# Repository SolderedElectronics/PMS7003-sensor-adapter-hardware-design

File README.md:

# PMS7003 sensor adapter Hardware Design

## About the Product

|  |
| :----------------------------------------------------------: |
| [Buy PMS7003 sensor adapter](https://www.solde.red/333058) |

To connect to our PMS7003 air quality sensor easily, we designed this adapter. It allows you to connect the PMS7003 sensor to breadboard or to connect with cables.

---

## Repository Contents

This repository contains all design files for PMS7003 sensor adapter, organized as follows:

- **`CAD` folder**: Contains KiCAD design files, including:
  - Schematics
  - PCB layout
  - Panel PCB layout
  - Source 3D files in Fusion360, if any
  - All files are sorted by version with a detailed change log.
- **`OUTPUTS` folder**: Includes all production-ready files, such as:
  - Bill of Materials (BOM) and interactive BOM (iBOM)
  - PDF versions of schematics
  - 3D `.step` file of the board
  - 3D-printable models
  - Gerber files for PCB manufacturing
  - Image of the pinout of the board
  - Product image
  - Compliance, legal and generic sales documents

Refer to the `Change Log` in the CAD folder for details about updates between versions.

---

## Learn More About the Product

Beyond the repository, explore the following resources:

### Soldered Verify

The **Soldered Verify** system ensures every board you purchase from Soldered is fully functional. It also provides access to exclusive test data for your product. To get started, find the unique Soldered Verify ID on your product's packaging and enter the ID on the [Soldered Verify page](https://soldered.com/verify/) to access test results and additional product details.

### Soldered Community

Soldered Community is your go-to place for technical support. Our engineers track and answer all questions posted there, and it’s a great space for the maker community. Get answers to your questions and solutions for your challenges at [Soldered Community](https://soldered.com/community).

### solde.red

solde.red is an ultimate URL shortener and information hub. Access it by typing solde.red/ followed by your product SKU, e.g., [solde.red/333000](https://solde.red/333000), to find getting-started guides, datasheets, open-source hardware and software files, certifications, images, pinouts, and more. Read more about the shortener [here](https://solde.red/info/).

---

## Contributing

Contributions are welcome! Here’s how you can get involved:

- Submit pull requests to enhance the design or fix issues.
- Report bugs or problems by opening an issue.

We encourage community collaboration to make this product even better.

---

## About Soldered

[Soldered for Makers](https://soldered.com) specializes in designing and manufacturing electronic products tailored for enthusiasts, ranging from hobbyists to professionals. Our portfolio includes electronic boards, sensors, and actuators that are widely utilized in fields such as microelectronics, mechatronics, robotics, programming, and IoT. Every product we offer is designed in-house and built upon open-source hardware and software platforms. Proudly certified and manufactured within the European Union, our catalog likely includes the product you need for your project.

We complement these products with comprehensive tutorials and manuals, product descriptions, schematics, programming codes, and project examples. Our round-the-clock [customer and technical support](https://soldered.com/community) is available for all our products, irrespective of the sales channel. Soldered’s success and services reflect our maker community’s unwavering [trust](https://www.trustpilot.com/review/soldered.com), for which we are deeply grateful. Join our community and create using Soldered products.

---

## License

All Soldered open-source hardware (OSH) is under The TAPR Open Hardware License. Read more in the LICENSE file located in this repository.

**Disclaimer:**

No warranty - all designs in this repository are distributed in the hope that they will be useful, but without any warranty. They are provided "AS IS", therefore without warranty of any kind, either expressed or implied. The entire quality and performance of what you do with the contents of this repository are your responsibility. In no event Soldered Electronics will be liable for your damages, or losses, including any general, special, incidental, or consequential damage arising out of the use or inability to use the contents of this repository. 

---

## Have fun!

Thank you for your support from your fellow makers at Soldered Electronics.

Happy Making!

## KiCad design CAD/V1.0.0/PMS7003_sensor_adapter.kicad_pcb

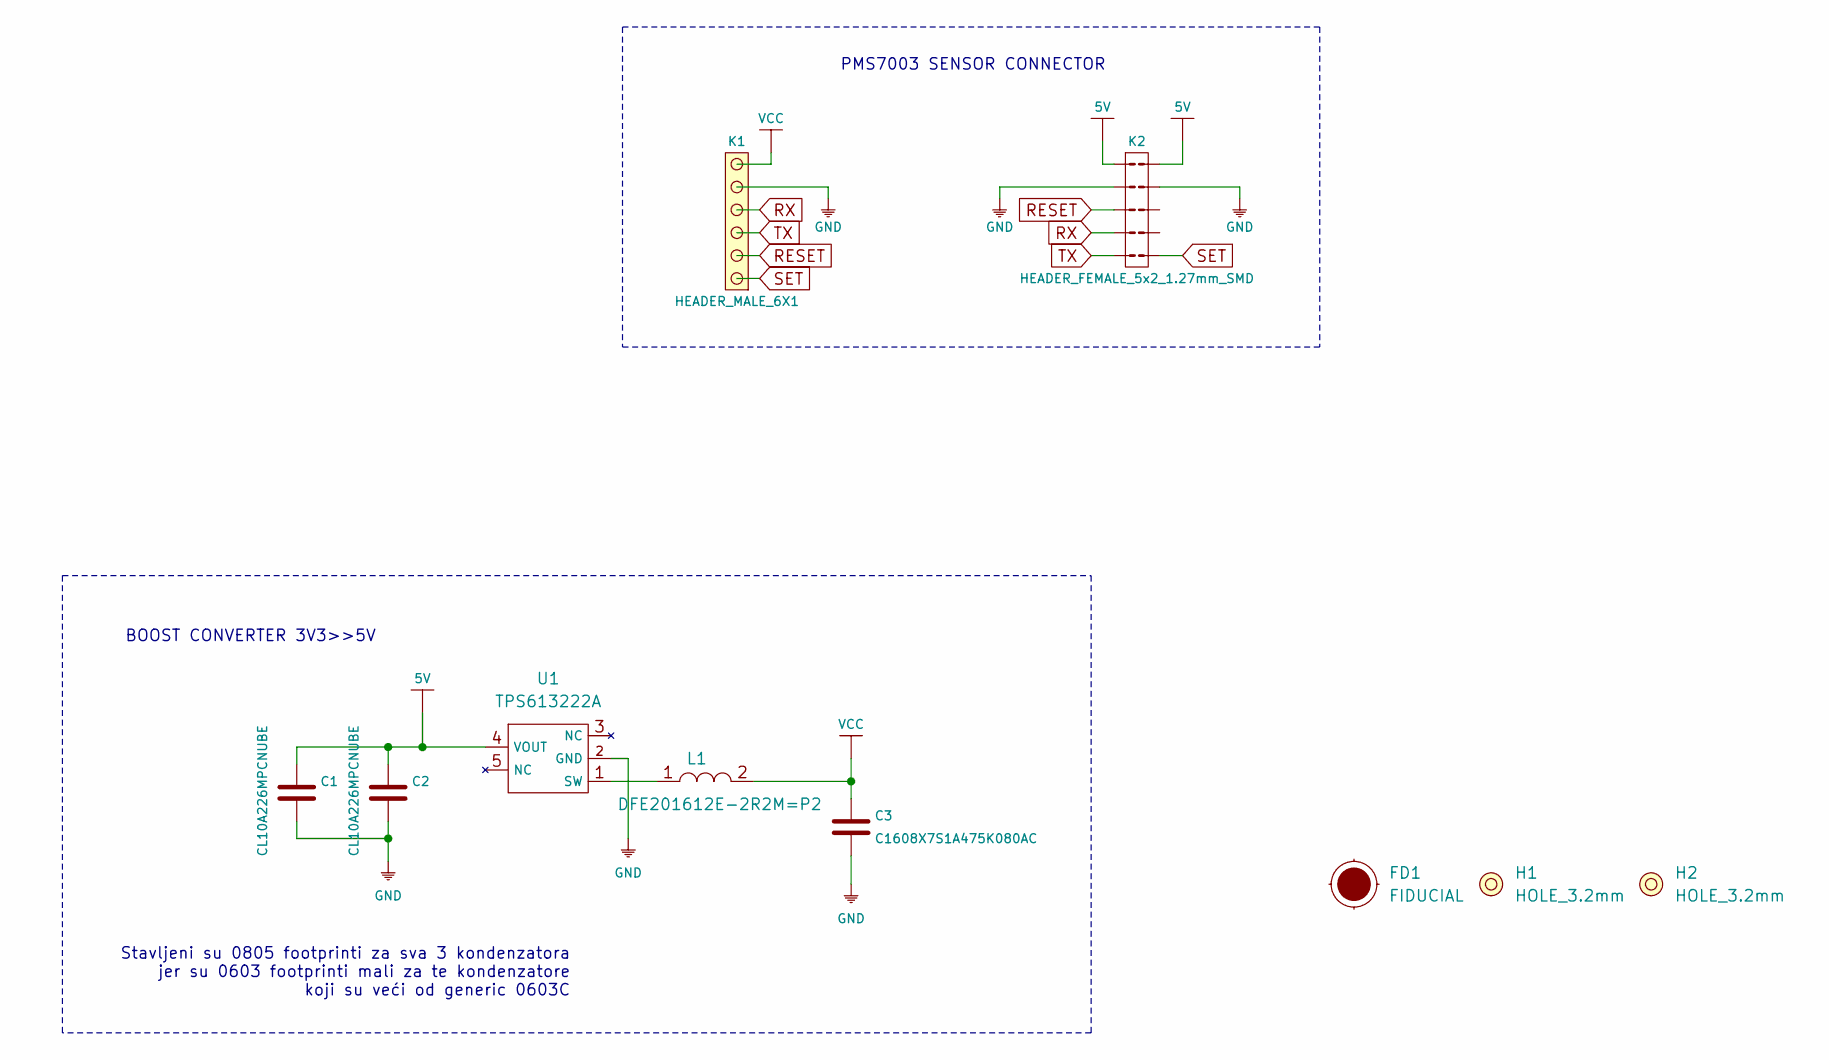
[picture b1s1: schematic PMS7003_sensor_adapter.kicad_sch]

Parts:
C1, C2: CL10A226MPCNUBE; 0805C
C3: C1608X7S1A475K080AC; 0805C
FD1: FIDUCIAL; FIDUCIAL_23
H1, H2: HOLE_3.2mm
K1: HEADER_MALE_6X1
K2: HEADER_FEMALE_5x2_1.27mm_SMD
L1: DFE201612E-2R2M=P2; 0806L
U1: TPS613222A; tps613222a

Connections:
5V: C1.2, C2.2, K2.1, K2.10, U1.4 (VOUT)
GND: C1.1, C2.1, C3.1, K1.5, K2.2, K2.9, U1.2 (GND)
unnamed: L1.1, U1.1 (SW)
RESET: K1.2, K2.3
RX: K1.4, K2.4
SET: K1.1, K2.6
TX: K1.3, K2.5
VCC: C3.2, K1.6, L1.2

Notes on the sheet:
BOOST CONVERTER 3V3>>5V
Stavljeni su 0805 footprinti za sva 3 kondenzatora jer su 0603 footprinti mali za te kondenzatore koji su veći od generic 0603C
PMS7003 SENSOR CONNECTOR

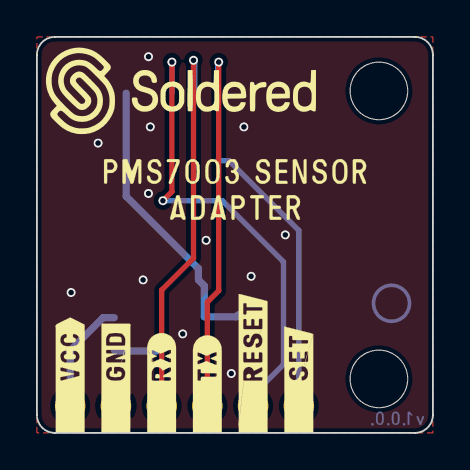
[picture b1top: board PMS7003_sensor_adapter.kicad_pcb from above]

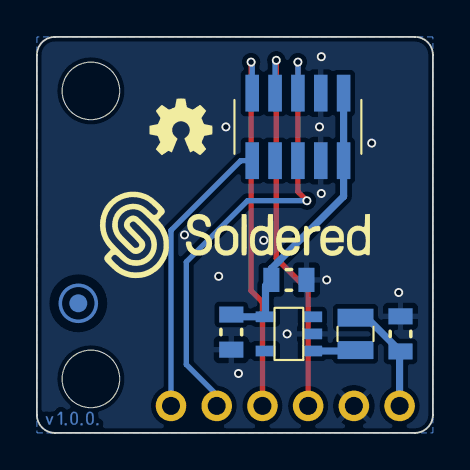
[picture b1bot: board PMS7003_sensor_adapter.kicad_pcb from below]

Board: 2 copper layers, 22.0 x 22.0 mm, 11 parts (8 on the bottom side), 8 nets.

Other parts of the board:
Ref**: Val**; Version1.0.0.

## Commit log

2022-08-06 Updating open source files.
